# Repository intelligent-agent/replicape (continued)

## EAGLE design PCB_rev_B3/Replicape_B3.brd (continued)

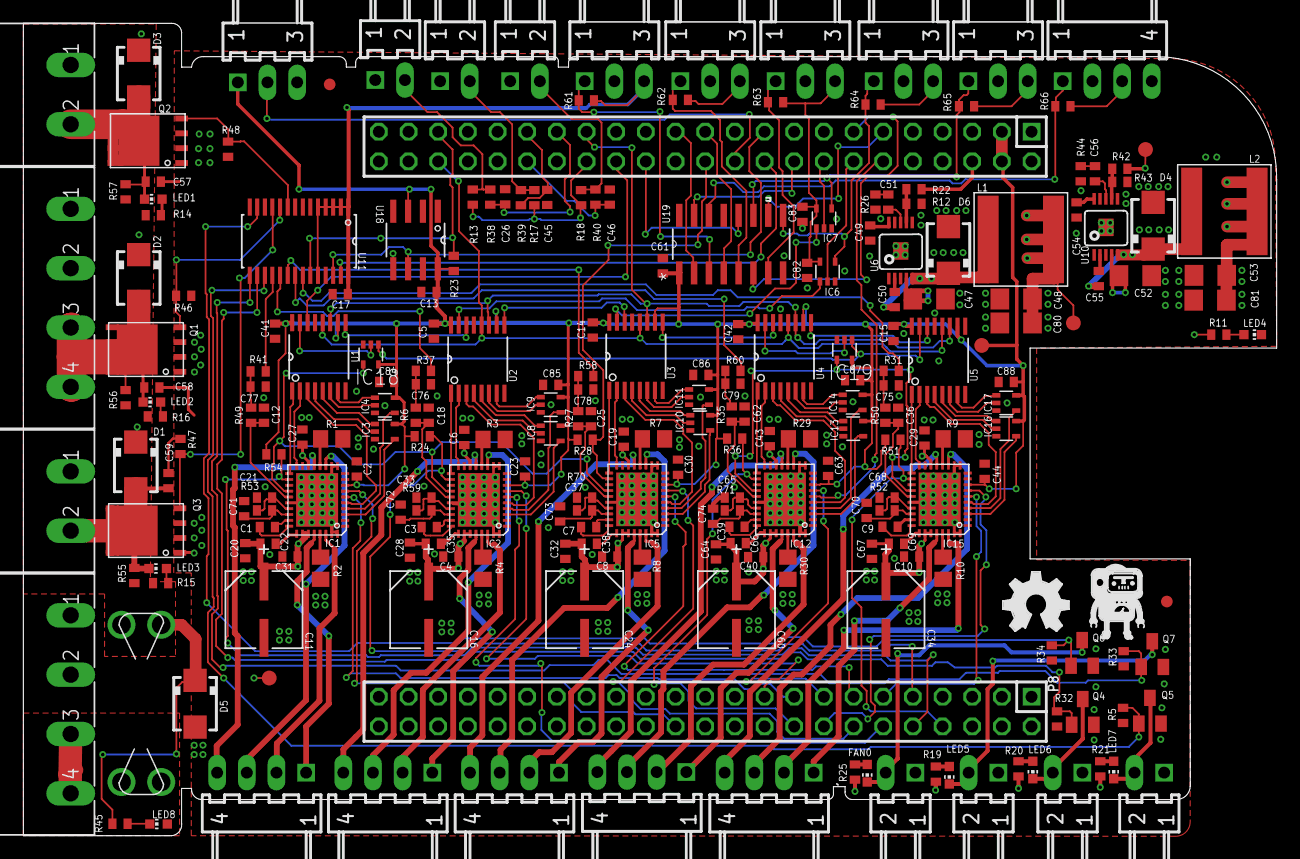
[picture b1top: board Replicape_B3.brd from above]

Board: 4 copper layers, 107.3 x 69.5 mm, 244 parts (0 on the bottom side), 210 nets.

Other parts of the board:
U$1: LOGO_BIG

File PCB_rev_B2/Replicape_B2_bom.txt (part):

Partlist exported from /home/elias/workspace/replicape/PCB_rev_B2/Replicape_B2.sch at 30.07.15 20:18

Qty Value                  Device                 Package              Parts                                                                                                                                                                                                                      Description                                                                       MF      MPN           OC_FARNELL OC_NEWARK PACKAGE  SUPPLIER          TOLERANCE TP_SIGNAL_NAME VALUE VOLTAGERATING
4                          NPN-TRANSISTOR_SOT23   SOT23                Q4, Q5, Q6, Q7                                                                                                                                                                                                             NPN TRANSISTOR                                                                                                                                                                                      
10  0.1R                   R-EU_R0805             R0805                R1, R2, R3, R4, R7, R8, R9, R10, R29, R30                                                                                                                                                                                  RESISTOR, European symbol                                                                                                                                                                           
45  0.1uF                  C-EUC0402              C0402                C2, C4, C5, C6, C8, C10, C13, C14, C15, C17, C19, C20, C22, C23, C27, C28, C29, C30, C31, C32, C35, C38, C40, C41, C42, C43, C44, C61, C63, C64, C66, C67, C69, C70, C71, C72, C73, C74, C82, C83, C84, C85, C86, C87, C88 CAPACITOR, European symbol                                                                                                                                                                          
5   100UF                  EEE-FK1V101XP-CASE-D8  CAPAE660X800N        C11, C16, C24, C34, C60                                                                                                                                                                                                    Aluminum Electrolytic Capacitors,Surface Mount Type                                       EEE-FK1V101XP 1850114    23T0869   CASE-D8  PANASONIC         ±20 %                    100UF 35V          
15  10K                    R-EU_R0402             R0402                R6, R22, R27, R31, R35, R37, R38, R39, R40, R41, R43, R49, R50, R58, R60                                                                                                                                                   RESISTOR, European symbol                                                                                                                                                                           
4   10nF                   C-EUC0402              C0402                C49, C50, C54, C55                                                                                                                                                                                                         CAPACITOR, European symbol                                                                                                                                                                          
6   10uF                   C-EUC1206              C1206                C47, C48, C52, C53, C80, C81                                                                                                                                                                                               CAPACITOR, European symbol                                                                                                                                                                          
1   120K                   R-EU_R0402             R0402                R42                                                                                                                                                                                                                        RESISTOR, European symbol                                                                                                                                                                           
2   1nF                    C-EUC0402              C0402                C51, C56                                                                                                                                                                                                                   CAPACITOR, European symbol                                                                                                                                                                          
5   2.2R                   R-EU_R0402             R0402                R52, R53, R59, R70, R71                                                                                                                                                                                                    RESISTOR, European symbol                                                                                                                                                                           
7   22-05-7028-02          22-05-7028-02          7395-02              X4, X5, X6, X7, X8, X9, X11                                                                                                                                                                                                CONNECTOR                                                                                               9731601    unknown                                                                          
6   22-05-7038-03          22-05-7038-03          7395-03              X1, X10, X13, X19, X22, X23                                                                                                                                                                                                CONNECTOR                                                                                               unknown    unknown                                                                          
6   22-05-7048-04          22-05-7048-04          7395-04              X12, X14, X15, X16, X17, X18                                                                                                                                                                                               CONNECTOR                                                                                               unknown    unknown                                                                          
5   22nF                   C-EUC0402              C0402                C1, C3, C7, C9, C39                                                                                                                                                                                                        CAPACITOR, European symbol                                                                                                                                                                          
2   33uH                   RT8040T330             NR8040T330           L1, L2                                                                                                                                                                                                                                                                                                                                                                                                                         
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
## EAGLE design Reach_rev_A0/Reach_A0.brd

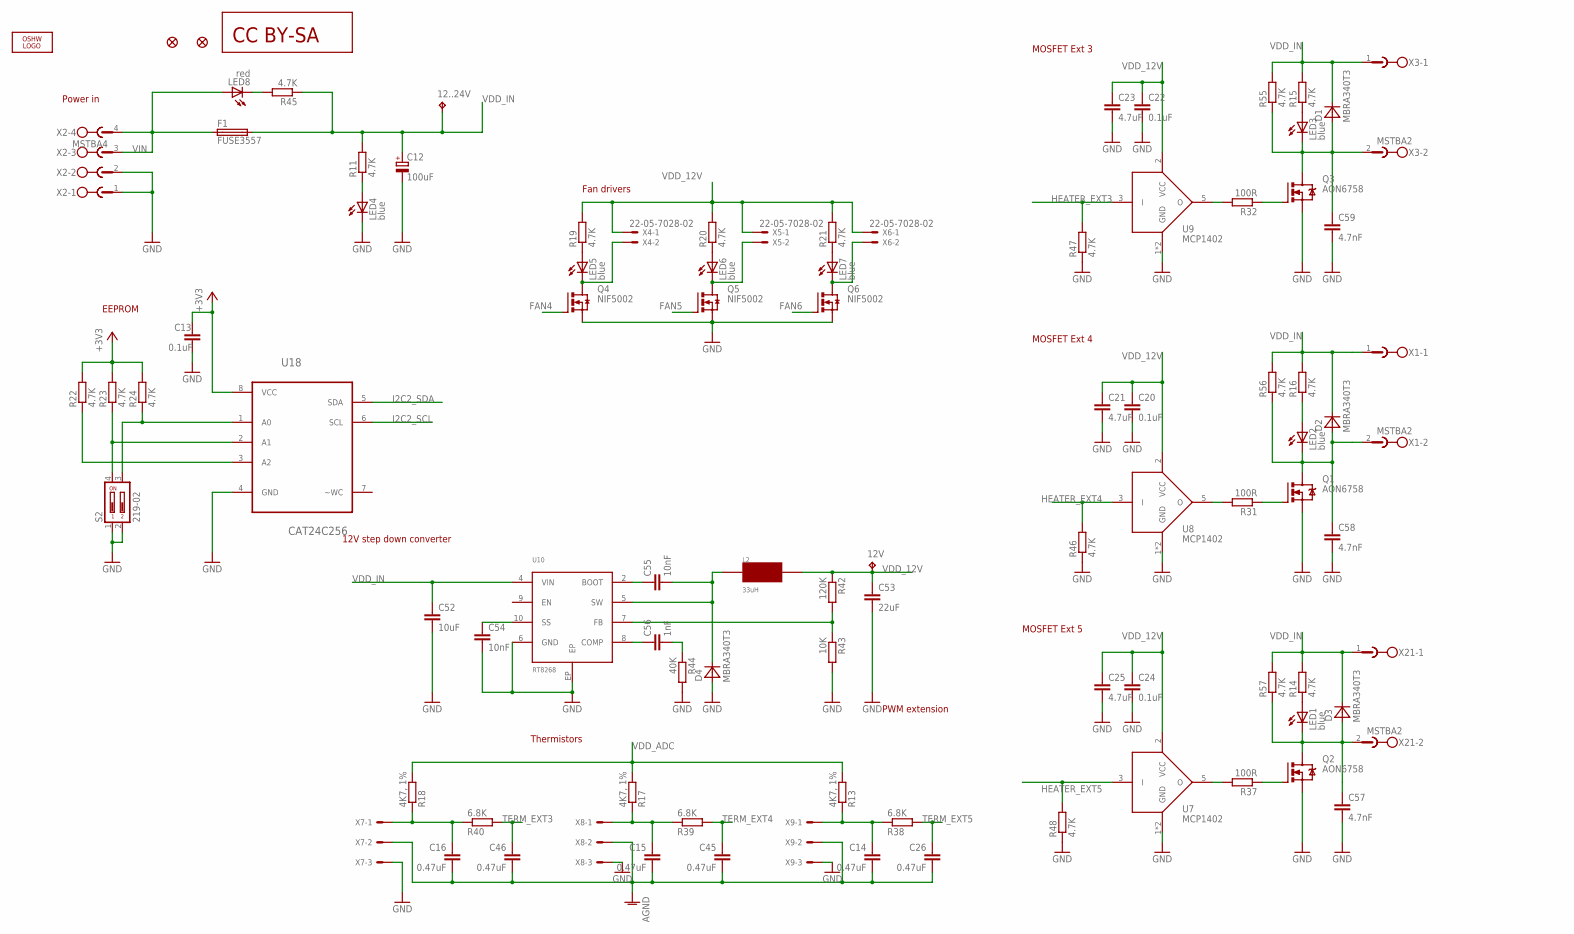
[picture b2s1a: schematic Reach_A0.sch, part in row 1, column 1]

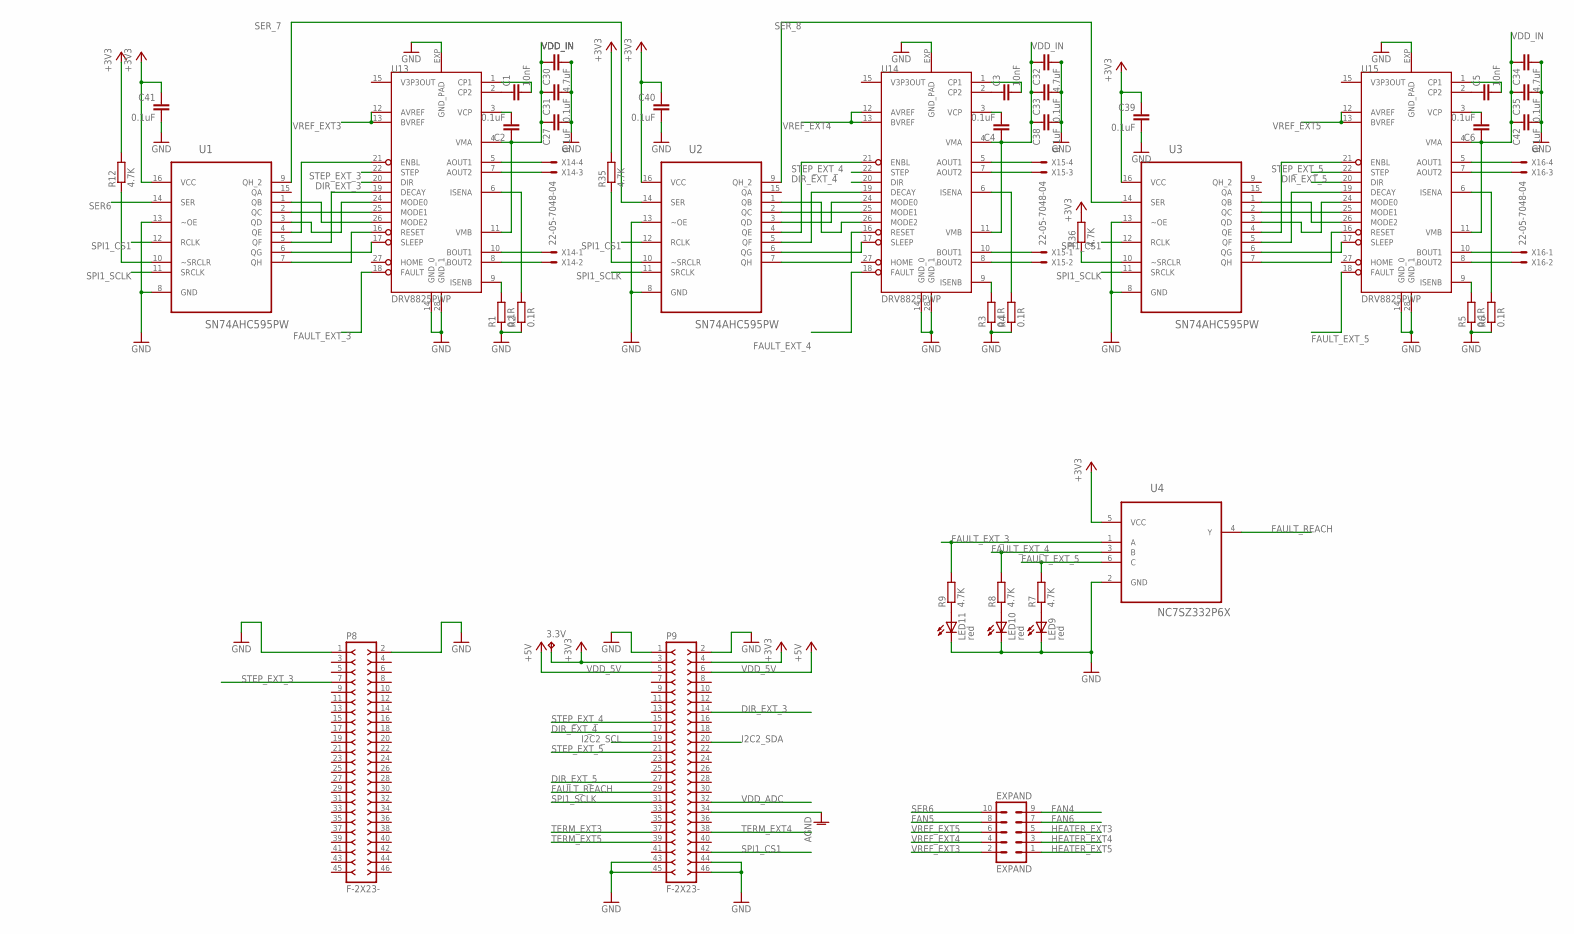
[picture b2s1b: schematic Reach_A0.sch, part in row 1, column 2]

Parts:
3.3V, 12..24V, 12V: TPB1,27; B1,27
C1, C3, C5, C54, C55: 10nF; C0402
C2, C4, C6, C13, C20, C22, C24, C27, C31, C33, C35, C38, C39, C40, C41, C42: 0.1uF; C0402
C12: 100uF; 140CLH-0810
C14, C15, C16, C26, C45, C46: 0.47uF; C0402
C21, C23, C25: 4.7uF; C0402
C30, C32, C34: 4.7uF; C0603
C52: 10uF; C1206
C53: 22uF; C0805
C56: 1nF; C0402
C57, C58, C59: 4.7nF; C0402
D1, D2, D3, D4: MBRA340T3; SMA
EXPAND: EXPAND; MA05-2
F1: FUSE3557; 3557
JP1, JP2: FIDUCIAL1X2.5; FIDUCIAL-1X2.5
L2: 33uH; NR8040T330
LED1, LED2, LED3, LED4, LED5, LED6, LED7: blue; CHIP-LED0603
LED8, LED9, LED10, LED11: red; CHIP-LED0603
LOGO1: OSHW_LOGO_FILLX0200-NT; OSHW_FILLX200_NOTEXT
P8, P9: F-2X23-; DIL-100-2X23
Q1, Q2, Q3: AON6758; 8-DFN-EP-(5X6)
Q4, Q5, Q6: NIF5002; SOT223
R1, R2, R3, R4, R5, R6: 0.1R; R0805
R7, R8, R9, R11, R12, R14, R15, R16, R19, R20, R21, R22, R23, R24, R35, R36, R45, R46, R47, R48, R55, R56, R57: 4.7K; R0402
R13, R17, R18: 4K7, 1%; R0402
R31, R32, R37: 100R; R0402
R38, R39, R40: 6.8K; R0402
R42: 120K; R0402
R43: 10K; R0402
R44: 40K; R0402
S2: 219-02; CTS-219-02
U1, U2, U3: SN74AHC595PW; SOP65P640X120-16N
U4: NC7SZ332P6X; SOT65P210X110-6N
U7, U8, U9: MCP1402; SOT23-5L
U10: RT8268; MSOP10
U13, U14, U15: DRV8825PWP; TSSOP-28
U18: CAT24C256; SOIC127P600X175-8N
U$3: CC-BY-SA
X1, X3, X21: MSTBA2
X2: MSTBA4
X4, X5, X6: 22-05-7028-02; 7395-02
X7, X8, X9: 22-05-7038-03; 7395-03
X14, X15, X16: 22-05-7048-04; 7395-04

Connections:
+3V3: 3.3V.TP, C13.1, C39.1, C40.1, C41.1, P9.3, P9.4, R12.2, R22.2, R23.2, R24.2, R35.2, R36.2, U1.16 (VCC), U2.16 (VCC), U3.16 (VCC), U4.5 (VCC), U18.8 (VCC)
A1_X: U13.5 (AOUT1), X14.4
A2_X: U13.7 (AOUT2), X14.3
AGND: C14.2, C15.2, C16.2, C26.2, C45.2, C46.2, P9.34, X7.2, X8.2, X9.2
B1_X: U13.10 (BOUT1), X14.1
DIR_EXT_3: P9.14, U13.20 (DIR)
DIR_EXT_4: P9.17, U14.20 (DIR)
DIR_EXT_5: P9.27, U15.20 (DIR)
FAN4: EXPAND.9, Q4.1 (G)
FAN5: EXPAND.8, Q5.1 (G)
FAN6: EXPAND.7, Q6.1 (G)
FAULT_EXT_3: R9.2, U4.1 (A), U13.18 (FAULT)
FAULT_EXT_4: R8.2, U4.3 (B), U14.18 (FAULT)
FAULT_EXT_5: R7.2, U4.6 (C), U15.18 (FAULT)
FAULT_REACH: P9.29, U4.4 (Y)
GND: C12.-, C13.2, C20.2, C21.2, C22.2, C23.2, C24.2, C25.2, C27.2, C30.2, C31.2, C32.2, C33.2, C34.2, C35.2, C38.2, C39.2, C40.2, C41.2, C42.2, C52.2, C53.2, C54.2, C57.2, C58.2, C59.2, D4.A, LED4.C, LED9.C, LED10.C, LED11.C, P8.1, P8.2, P9.1, P9.2, P9.43, P9.44, P9.45, P9.46, Q1.1 (S), Q1.2 (S), Q1.3 (S), Q2.1 (S), Q2.2 (S), Q2.3 (S), Q3.1 (S), Q3.2 (S), Q3.3 (S), Q4.3 (S), Q5.3 (S), Q6.3 (S), R1.1, R2.1, R3.1, R4.1, R5.1, R6.1, R43.2, R44.2, R46.1, R47.1, R48.1, S2.1, S2.2, U1.8 (GND), U1.13 (~OE), U2.8 (GND), U2.13 (~OE), U3.8 (GND), U3.13 (~OE), U4.2 (GND), U7.1 (GND), U7.4 (GND), U8.1 (GND), U8.4 (GND), U9.1 (GND), U9.4 (GND), U10.6 (GND), U10.EP, U13.14 (GND_0), U13.28 (GND_1), U13.EXP (GND_PAD), U14.14 (GND_0), U14.28 (GND_1), U14.EXP (GND_PAD), U15.14 (GND_0), U15.28 (GND_1), U15.EXP (GND_PAD), U18.4 (GND), X2.1, X2.2, X7.3, X8.3, X9.3
HEATER_EXT3: EXPAND.5, R47.2, U9.3 (I)
HEATER_EXT4: EXPAND.3, R46.2, U8.3 (I)
HEATER_EXT5: EXPAND.1, R48.2, U7.3 (I)
I2C2_SCL: P9.19, U18.6 (SCL)
I2C2_SDA: P9.20, U18.5 (SDA)
unnamed: U13.8 (BOUT2), X14.2
unnamed: U14.8 (BOUT2), X15.2
unnamed: U15.10 (BOUT1), X16.1
unnamed: U15.8 (BOUT2), X16.2
unnamed: LED9.A, R7.1
unnamed: LED8.C, R45.2
unnamed: LED5.A, R19.1
unnamed: LED10.A, R8.1
unnamed: LED11.A, R9.1
unnamed: C1.1, U13.2 (CP2)
unnamed: C1.2, U13.1 (CP1)
unnamed: R1.2, U13.9 (ISENB)
unnamed: R2.2, U13.6 (ISENA)
unnamed: R32.2, U9.5 (O)
unnamed: C2.2, U13.3 (VCP)
unnamed: Q2.4 (G), R37.1
unnamed: C3.1, U14.2 (CP2)
unnamed: C3.2, U14.1 (CP1)
unnamed: R3.2, U14.9 (ISENB)
unnamed: R4.2, U14.6 (ISENA)
unnamed: C4.2, U14.3 (VCP)
unnamed: R37.2, U7.5 (O)
unnamed: C5.1, U15.2 (CP2)
unnamed: C5.2, U15.1 (CP1)
unnamed: R5.2, U15.9 (ISENB)
unnamed: R6.2, U15.6 (ISENA)
unnamed: C6.2, U15.3 (VCP)
unnamed: Q1.4 (G), R31.1
unnamed: R31.2, U8.5 (O)
unnamed: C57.1, D3.A, LED1.C, Q2.5 (D), Q2.6 (D), Q2.7 (D), Q2.8 (D), Q2.TH (D), R57.1, X21.2
unnamed: LED4.A, R11.1
unnamed: R12.1, U1.10 (~SRCLR)
unnamed: R35.1, U2.10 (~SRCLR)
unnamed: R36.1, U3.10 (~SRCLR)
unnamed: LED7.C, Q6.2 (D), Q6.4 (D), X6.2
unnamed: LED6.C, Q5.2 (D), Q5.4 (D), X5.2
unnamed: LED5.C, Q4.2 (D), Q4.4 (D), X4.2
unnamed: LED6.A, R20.1
unnamed: LED7.A, R21.1
unnamed: LED3.A, R15.1
unnamed: LED1.A, R14.1
unnamed: LED2.A, R16.1
unnamed: Q3.4 (G), R32.1
unnamed: R24.1, S2.3, U18.1 (A0)
unnamed: R23.1, S2.4, U18.2 (A1)
unnamed: R22.1, U18.3 (A2)
unnamed: R42.2, R43.1, U10.7 (FB)
unnamed: C59.1, D1.A, LED3.C, Q3.5 (D), Q3.6 (D), Q3.7 (D), Q3.8 (D), Q3.TH (D), R55.1, X3.2
unnamed: C14.1, R13.1, R38.1, X9.1
unnamed: C55.2, D4.C, L2.P$2, U10.5 (SW)
unnamed: C16.1, R18.1, R40.1, X7.1
unnamed: C15.1, R17.1, R39.1, X8.1
unnamed: C58.1, D2.A, LED2.C, Q1.5 (D), Q1.6 (D), Q1.7 (D), Q1.8 (D), Q1.TH (D), R56.1, X1.2
unnamed: C54.1, U10.10 (SS)
unnamed: C56.1, U10.8 (COMP)
unnamed: C55.1, U10.2 (BOOT)
unnamed: C56.2, R44.1
SER6: EXPAND.10, U1.14 (SER)
SER_7: U1.9 (QH_2), U2.14 (SER)
SER_8: U2.9 (QH_2), U3.14 (SER)
SPI1_CS1: P9.42, U1.12 (RCLK), U2.12 (RCLK), U3.12 (RCLK)
SPI1_SCLK: P9.31, U1.11 (SRCLK), U2.11 (SRCLK), U3.11 (SRCLK)
STEP1_Y: U14.5 (AOUT1), X15.4
STEP1_Z: U15.5 (AOUT1), X16.4
STEP2_Y: U14.7 (AOUT2), X15.3
STEP2_Z: U15.7 (AOUT2), X16.3
STEP3_Y: U14.10 (BOUT1), X15.1
STEP_EXT_3: P8.7, U13.22 (STEP)
STEP_EXT_4: P9.15, U14.22 (STEP)
STEP_EXT_5: P9.21, U15.22 (STEP)
TERM_EXT3: C46.1, P9.37, R40.2
TERM_EXT4: C45.1, P9.38, R39.2
TERM_EXT5: C26.1, P9.39, R38.2
VDD_5V: P9.5, P9.6
VDD_12V: 12V.TP, C20.1, C21.1, C22.1, C23.1, C24.1, C25.1, C53.1, L2.P$1, R19.2, R20.2, R21.2, R42.1, U7.2 (VCC), U8.2 (VCC), U9.2 (VCC), X4.1, X5.1, X6.1
VDD_ADC: P9.32, R13.2, R17.2, R18.2
VDD_IN: 12..24V.TP, C2.1, C4.1, C6.1, C12.+, C27.1, C30.1, C31.1, C32.1, C33.1, C34.1, C35.1, C38.1, C42.1, C52.1, D1.C, D2.C, D3.C, F1.3 (2), F1.4 (2), R11.2, R14.2, R15.2, R16.2, R45.1, R55.2, R56.2, R57.2, U10.4 (VIN), U13.4 (VMA), U13.11 (VMB), U14.4 (VMA), U14.11 (VMB), U15.4 (VMA), U15.11 (VMB), X1.1, X3.1, X21.1
VIN: F1.1, F1.2 (1), LED8.A, X2.3, X2.4
VREF_EXT3: EXPAND.2, U13.12 (AVREF), U13.13 (BVREF)
VREF_EXT4: EXPAND.4, U14.12 (AVREF), U14.13 (BVREF)
VREF_EXT5: EXPAND.6, U15.12 (AVREF), U15.13 (BVREF)
X_DECAY: U1.5 (QF), U13.19 (DECAY)
X_MODE0: U1.3 (QD), U13.24 (MODE0)
X_MODE1: U1.2 (QC), U13.25 (MODE1)
X_MODE2: U1.1 (QB), U13.26 (MODE2)
X_NENABLE: U1.4 (QE), U13.21 (ENBL)
X_NRESET: U1.7 (QH), U13.16 (RESET)
X_NSLEEP: U1.6 (QG), U13.17 (SLEEP)
Y_DECAY: U2.5 (QF), U14.19 (DECAY)
Y_MODE0: U2.3 (QD), U14.24 (MODE0)
Y_MODE1: U2.2 (QC), U14.25 (MODE1)
Y_MODE2: U2.1 (QB), U14.26 (MODE2)
Y_NENABLE: U2.4 (QE), U14.21 (ENBL)
Y_NRESET: U2.7 (QH), U14.16 (RESET)
Y_NSLEEP: U2.6 (QG), U14.17 (SLEEP)
Z_DECAY: U3.5 (QF), U15.19 (DECAY)
Z_MODE0: U3.3 (QD), U15.24 (MODE0)
Z_MODE1: U3.2 (QC), U15.25 (MODE1)
Z_MODE2: U3.1 (QB), U15.26 (MODE2)
Z_NENABLE: U3.4 (QE), U15.21 (ENBL)
Z_NRESET: U3.7 (QH), U15.16 (RESET)
Z_NSLEEP: U3.6 (QG), U15.17 (SLEEP)

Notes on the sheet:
Fan drivers
Power in
MOSFET Ext 3
MOSFET Ext 4
MOSFET Ext 5
Thermistors
EEPROM
PWM extension
12V step down converter

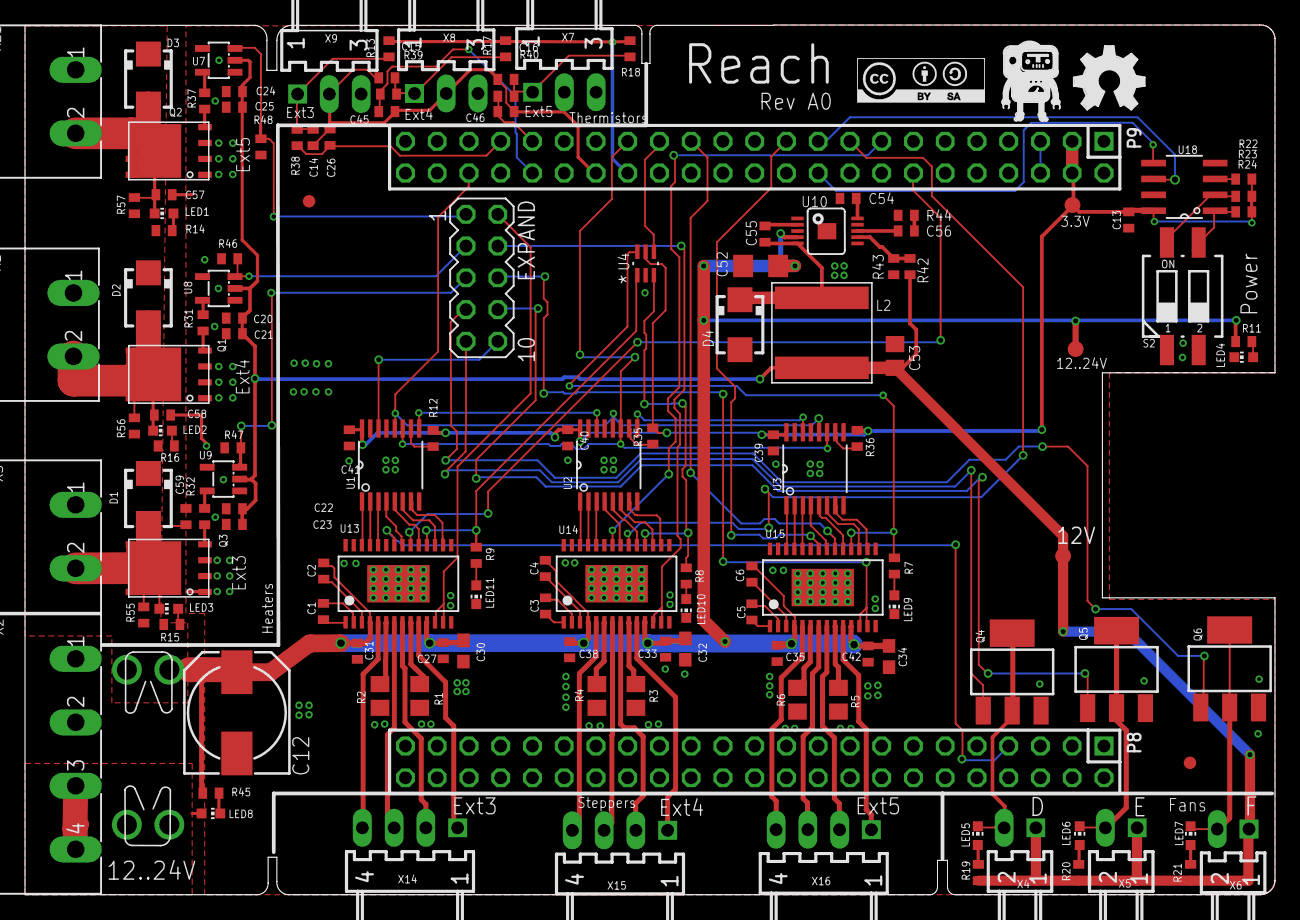
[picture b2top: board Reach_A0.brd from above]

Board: 2 copper layers, 100.0 x 69.6 mm, 141 parts (0 on the bottom side), 123 nets.

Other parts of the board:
U$1: LOGO_BIG

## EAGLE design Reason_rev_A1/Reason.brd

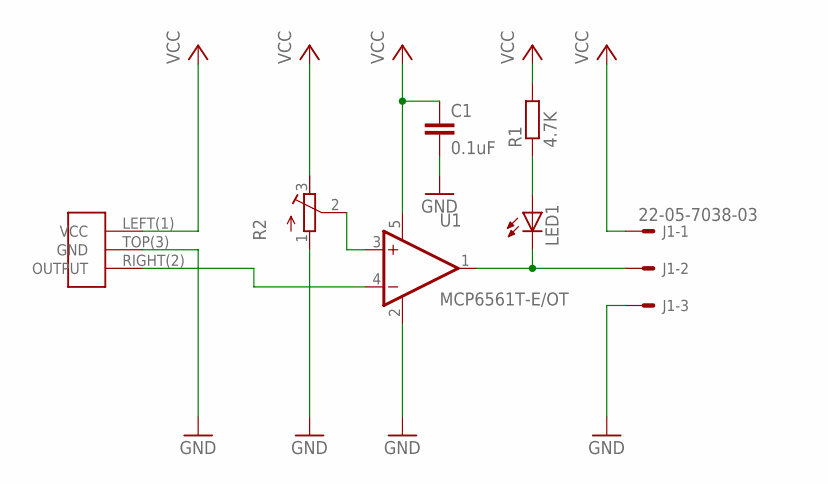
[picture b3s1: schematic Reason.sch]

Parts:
C1: 0.1uF; C0402
J1: 22-05-7038-03; 7395-03
LED1: LEDCHIPLED_0603; CHIPLED_0603
R1: 4.7K; R0402
R2: R-TRIMM5W; RTRIM5W
U1: MCP6561T-E/OT; SOT95P270X145-5N
U2: SS39ET; SOT-23

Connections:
GND: C1.2, J1.3, R2.1 (E), U1.2 (VSS), U2.TOP(3) (GND)
unnamed: J1.2, LED1.C, U1.1 (VOUT)
unnamed: LED1.A, R1.1
unnamed: R2.2 (S), U1.3 (VIN+)
unnamed: U1.4 (VIN-), U2.RIGHT(2) (OUTPUT)
VCC: C1.1, J1.1, R1.2, R2.3 (A), U1.5 (VDD), U2.LEFT(1) (VCC)

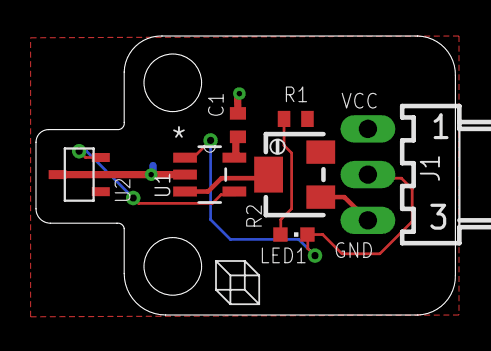
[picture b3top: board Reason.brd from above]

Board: 2 copper layers, 23.3 x 15.5 mm, 7 parts (0 on the bottom side), 6 nets.

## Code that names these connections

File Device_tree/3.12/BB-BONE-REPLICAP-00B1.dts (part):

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            };					
            pruicss_stepper_pins: pinmux_pruicss_stepper_pins{
                pinctrl-single,pins = <
                    0x038 0x07 // P8_16 (3)  = DIR_H     	= GPIO1_14
                    0x03C 0x07 // P8_15 (4)  = DIR_E    	= GPIO1_15
                    0x028 0x07 // P8_14 (5)  = DIR_Z   	 	= GPIO0_26
                    0x02C 0x07 // P8_17 (6)  = STEP_X 	 	= GPIO0_27
                    0x034 0x07 // P8_11 (22) = step_H    	= GPIO1_13	
                    0x030 0x07 // P8_12 (23) = Step_y	 	= GPIO1_12
                    0x024 0x07 // P8_13 (24) = Step_z	 	= GPIO0_23
                    0x020 0x07 // P8_19 (25) = Dir_y 	 	= GPIO0_22
                    0x07C 0x07 // P8_26      = Dir_x		= GPIO1_29
                    0x078 0x07 // P9_12      = step E    	= GPIO1_28
                >;
            };		
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            pinctrl-0 	  = <&pruicss_stepper_pins>;

            stepper_x{
                pin-names 	= "Replic:pru-step_x", "Replic:pru-dir_x";		
                gpios 		= <&gpio0 27 0
		                 	   &gpio1 29 0>; 
            };			
            stepper_y{
                pin-names 	= "Replic:pru-step_y", "Replic:pru-dir_y";		
                gpios 		=<&gpio1 12 0
		                 	  &gpio0 22 0>; 
            };
            stepper_z{
                pin-names 	= "Replic:pru-step_z", "Replic:pru-dir_z";		
                gpios 		= <&gpio0 23 0
		                 	   &gpio0 26 0>; 
            };
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
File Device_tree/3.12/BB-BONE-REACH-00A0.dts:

/*
 * Copyright (C) 2013 Intelligent Agent AS	<elias@iagent.no>
 *
 * This program is free software; you can redistribute it and/or modify
 * it under the terms of the GNU General Public License version 2 as
 * published by the Free Software Foundation.
 */



/dts-v1/;
/plugin/;

/ {
    compatible = "ti,beaglebone", "ti,beaglebone-black";

    /* identification */
    part-number = "BB-BONE-REACH";
    version = "00A0";

    /* state the resources this cape uses */
    exclusive-use =
        /* the pin header P8 uses */
        "P8.7",  /* STEP_EXT_3	*/
        /* the pin header P9 uses */
        "P9.14", /* DIR_EXT_3	*/
        "P9.15", /* STEP_EXT_4	*/
        "P9.17", /* DIR_EXT_4	*/
        "P9.21", /* STEP_EXT_5	*/
        "P9.26", /* FAULT_REACH	*/
        "P9.27"; /* DIR_EXT_5	*/

    fragment@0 {
        target = <&am33xx_pinmux>;
        __overlay__ {
            pruicss_stepper_pins_reach: pinmux_pruicss_stepper_pins_reach{
                pinctrl-single,pins = <
                    0x090 0x07 // P8_7  ()  = STEP_EXT_3	= GPIO2_2
                    0x048 0x07 // P9_14 ()  = DIR_EXT_3 	= GPIO1_18
                    0x040 0x07 // P9_15 ()  = STEP_EXT_4    = GPIO1_16
                    0x15C 0x07 // P9_17 ()  = DIR_EXT_4     = GPIO0_5
                    0x154 0x07 // P9_21 ()  = STEP_EXT_5    = GPIO0_3
                    0x1A4 0x07 // P9_27 ()  = DIR_EXT_5     = GPIO3_19
                >;
            };		

            stepper_fault_pins_reach: pinmux_stepper_fault_pins_reach{
                pinctrl-single,pins = <
                    0x180 0x37 // P9_26 = FAULT_REACH 	= GPIO0_14
                >;
            };
        };
    };

    fragment@1{
        target = <&pruss>;
        __overlay__{
            status = "okay";
            pinctrl-names = "default";
            pinctrl-0 	  = <&pruicss_stepper_pins_reach>;

            stepper_ext_3{
                pin-names 	= "Reach:pru-step_ext_3", "Reach:pru-dir_ext_3";		
                gpios 		= <&gpio2 2 0
		                 	   &gpio1 18 0>; 
            };			
            stepper_ext_4{
                pin-names 	= "Reach:pru-step_ext_4", "Reach:pru-dir_ext_4";		
                gpios 		=<&gpio1 16 0
		                 	  &gpio0 5 0>; 
            };
            stepper_ext_5{
                pin-names 	= "Reach:pru-step_ext_5", "Reach:pru-dir_ext_5";		
                gpios 		= <&gpio0 3 0
		                 	   &gpio3 19 0>; 
            };
        };
    };

    fragment@2 {
        target = <&baseboard_beaglebone_black>;
        __overlay__ {			
            #address-cells = <1>;
            #size-cells = <1>;							

            gpio_keys {
                compatible = "gpio-keys";
                pinctrl-names = "default";
                pinctrl-0 = <&stepper_fault_pins_reach>;
                #address-cells = <1>;
                #size-cells = <0>;
               
                fault_reach {
                    label               = "Reach:Fault";
                    debounce_interval   = <50>;
                    linux,code          = <95>;
                    gpios               = <&gpio0 14 0x5>;
                    gpio-key,wakeup;	
                };
            };
        };
    };

    fragment@3 {
        target = <&tscadc>;
        __overlay__ {			
            status = "okay";
            adc {
                ti,adc-channels = <0 1 2 3 4 5 6 7>;
            };
        };
    };
};

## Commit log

2013-11-18 Pushing before deleting the software. It has been moed to the redeem repository'
2013-11-18 Redid the readme, added a license file, deleted the software
2014-01-12 Added a new Device tree overlay file for Kernel 3.12
2014-01-23 Apparently some indent problems has been fixed on the DTO
2014-01-27 Added the inital revision of Reach (rev A0). The GERBER shoudl be ok, likewise the pin diagram and the BOM, but the pin-mux and wire diagrams are not updated.
2014-02-04 Changed device tree files to kernel 3.12 and cleaned up a bit
2014-04-16 Made A4A eeprom and added the binary files as well
2014-05-09 Added a test script and a service to test Replicape
2014-05-13 Added a Readh overlay and eeprom
2014-05-13 The A4A dts file had been copied frmo 3.12 instead of 3.8
2014-05-13 changed case on folder in systemd script
2014-05-13 Typo on folder name
2014-05-14 updated the test script with microstepping and also to use fixed pipe names
2014-05-16 Added all channels to reach
2014-08-26 Still working on the requirements
2014-09-03 Added first version of Reason hall effect end stop sensor
2014-09-20 New Reason, bigger holes.
2015-05-03 Added first version of Replicape Rev B1
2015-05-03 Fixed thermals
2015-05-06 Added eagleup
2015-05-06 Added first version of Sketchup file
2015-05-07 Added the last components to the PCB and made a pretty picture of it
2015-05-28 Made an EEPROM file for Rev B1
2015-06-15 First attempt at cape overlay for 00B1
2015-08-19 Added EEPROM for developer edition
2015-08-19 New location for eeprom in sys
2015-08-28 Added 00B2 eeprim
2015-08-28 Wrong path due to kernel 4.1
2015-09-09 Added Rev B2
2015-09-09 Made Sketchup model of eagle file
2015-10-02 Added Eagleup files for A4A
2015-10-02 Added skp for A4A
2015-10-09 Added the centroid, ready for sedning in files.
2015-10-09 Added some PDFs for easy online preview
2015-10-28 Started on REach for rev B
2015-12-08 Updated the test script
2015-12-08 Working test script
2015-12-08 Updated readmen
2015-12-23 Disable steppers after testing
2016-07-06 Added new version eeprom data
2016-07-12 Updated testing proc
2016-09-22 Added a Sketchup model
2017-01-23 Added a Collada (DAE) file
2017-01-31 Added .stl
2017-02-17 Added latest revison
2017-09-15 Committing Rev B4, and cleaning up old stuff before moving repo
2017-12-21 Added components placement file
